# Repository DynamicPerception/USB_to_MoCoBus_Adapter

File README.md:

USB_to_MoCoBus_Adapter
======================

EAGLE files for USB to RS-485 adapter used to connect directly from a computer to the MoCoBus

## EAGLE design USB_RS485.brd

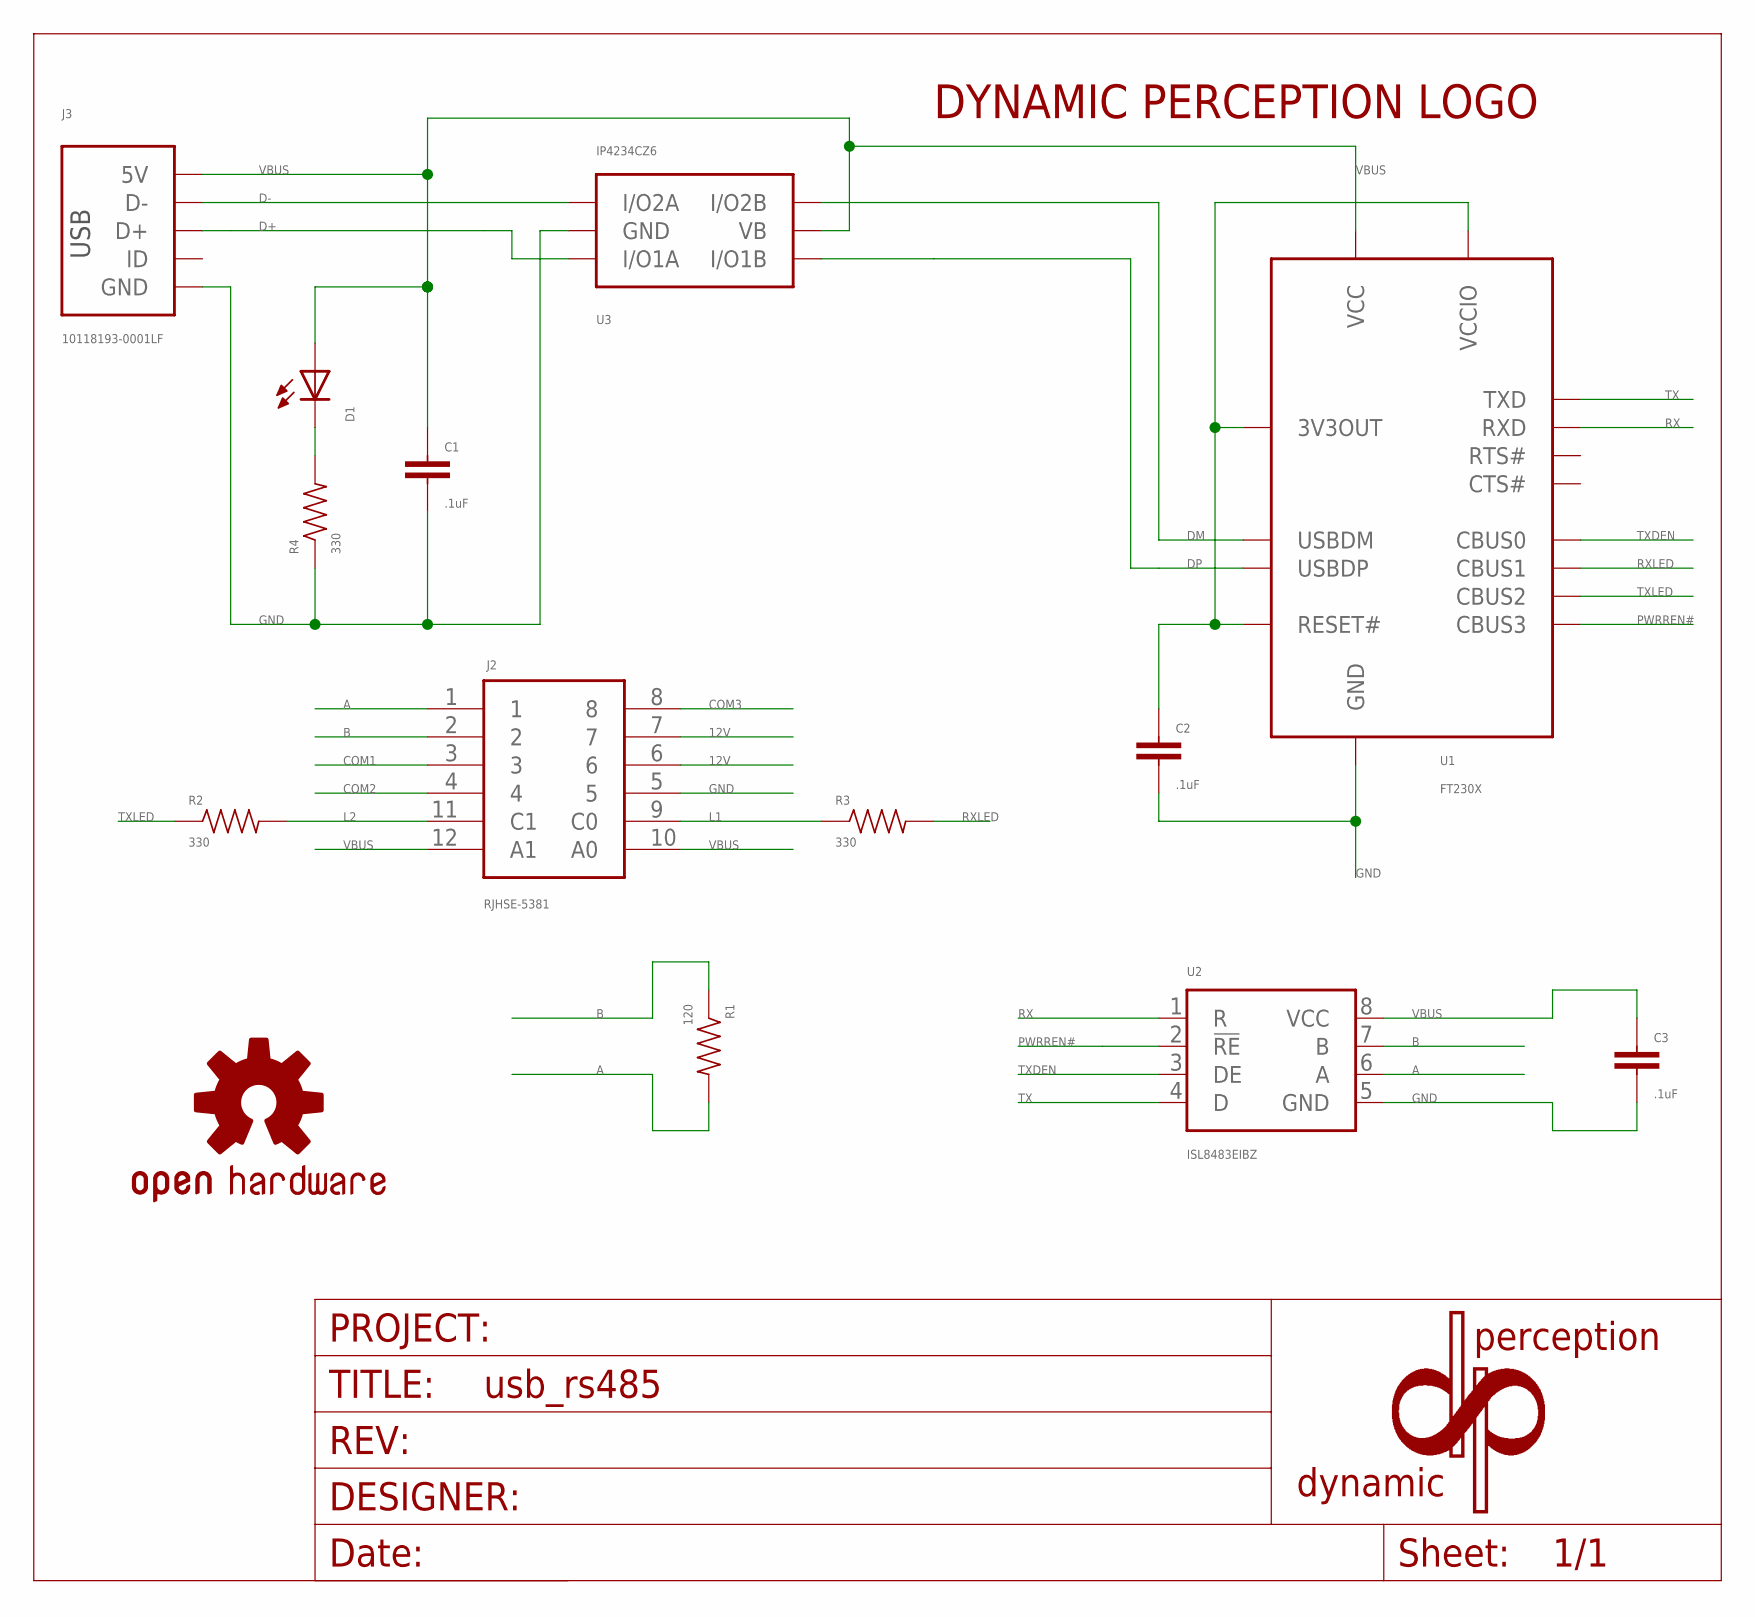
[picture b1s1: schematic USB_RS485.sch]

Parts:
C1, C2, C3: .1uF; 0402_CAP
D1: LEDSML0603; SML0603
J2: RJHSE-5381; RIGHT_ANGLE
J3: 10118193-0001LF
LOGO1: DP_LOGOSMALL; DP_LOGO_SMALL
R1: 120; 0402_RES
R2, R3, R4: 330; 0402_RES
U1: FT230X; SSOP-16
U2: ISL8483EIBZ; SO-08; MPN SN65176BD
U3: IP4234CZ6; SOT-457
U$1: OSHW-LOGOS; OSHW-LOGO-S
U$2: DP_FRAME

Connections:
12V: J2.6, J2.7
A: J2.1, R1.2, U2.6 (A)
B: J2.2, R1.1, U2.7 (B)
COM1: J2.3
COM2: J2.4
COM3: J2.8
D+: J3.3 (D+), U3.1 (I/O1A)
D-: J3.2 (D-), U3.6 (I/O2A)
DM: U1.9 (USBDM), U3.4 (I/O2B)
DP: U1.8 (USBDP), U3.3 (I/O1B)
GND: C1.2, C2.2, C3.2, J2.5, J3.5 (GND), J3.S1 (GND), J3.S2 (GND), J3.S3 (GND), J3.S4 (GND), R4.1, U1.5 (GND), U1.13 (GND), U2.5 (GND), U3.2 (GND)
L1: J2.9 (C0), R3.1
L2: J2.11 (C1), R2.2
unnamed: D1.C, R4.2
unnamed: C2.1, U1.3 (VCCIO), U1.10 (3V3OUT), U1.11 (RESET#)
PWRREN#: U1.16 (CBUS3), U2.2 (!RE)
RX: U1.4 (RXD), U2.1 (R)
RXLED: R3.2, U1.14 (CBUS1)
TX: U1.1 (TXD), U2.4 (D)
TXDEN: U1.15 (CBUS0), U2.3 (DE)
TXLED: R2.1, U1.7 (CBUS2)
VBUS: C1.1, C3.1, D1.A, J2.10 (A0), J2.12 (A1), J3.1 (5V), U1.12 (VCC), U2.8 (VCC), U3.5 (VB)

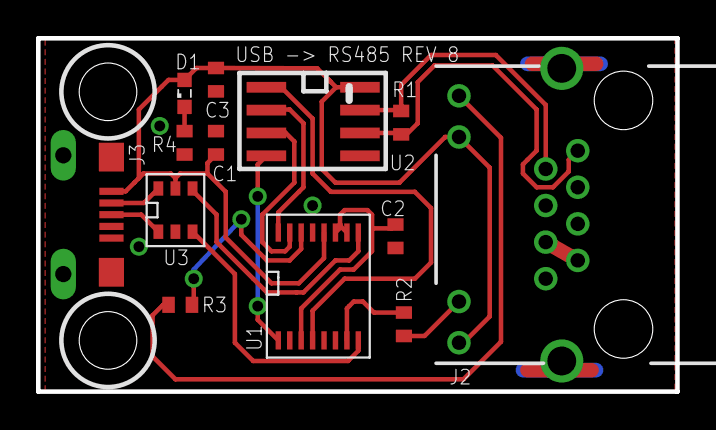
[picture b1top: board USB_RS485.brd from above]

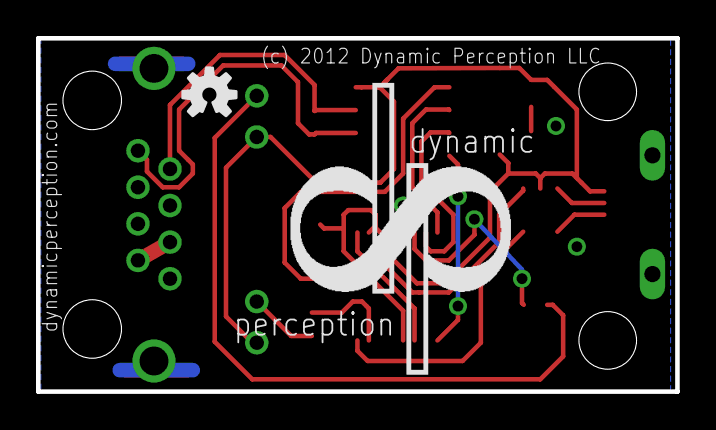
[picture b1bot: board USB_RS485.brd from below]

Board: 2 copper layers, 35.5 x 19.6 mm, 16 parts (2 on the bottom side), 19 nets.

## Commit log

2014-09-18 Board and schematic upload

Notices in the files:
USB_RS485.brd:
(c) 2012 Dynamic Perception LLC
parts and their libraries:
SparkFun-Aesthetics: Licensing: CC v3.0 Share-Alike You are welcome to use this library for commercial purposes.
